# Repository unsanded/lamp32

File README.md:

<big>CC3000 wifi lamp</big>

Basically a lamp with 5 colours, a bulb, controlled over wifi.

Currently i am strugling with bugs in the cc3000 module. Even TI recomend using the cc3100 instead, but i already had my cc3000 module before that. 
I will try to update the firmware, because that might fix some bugs. I don't however have an official patch programmer.

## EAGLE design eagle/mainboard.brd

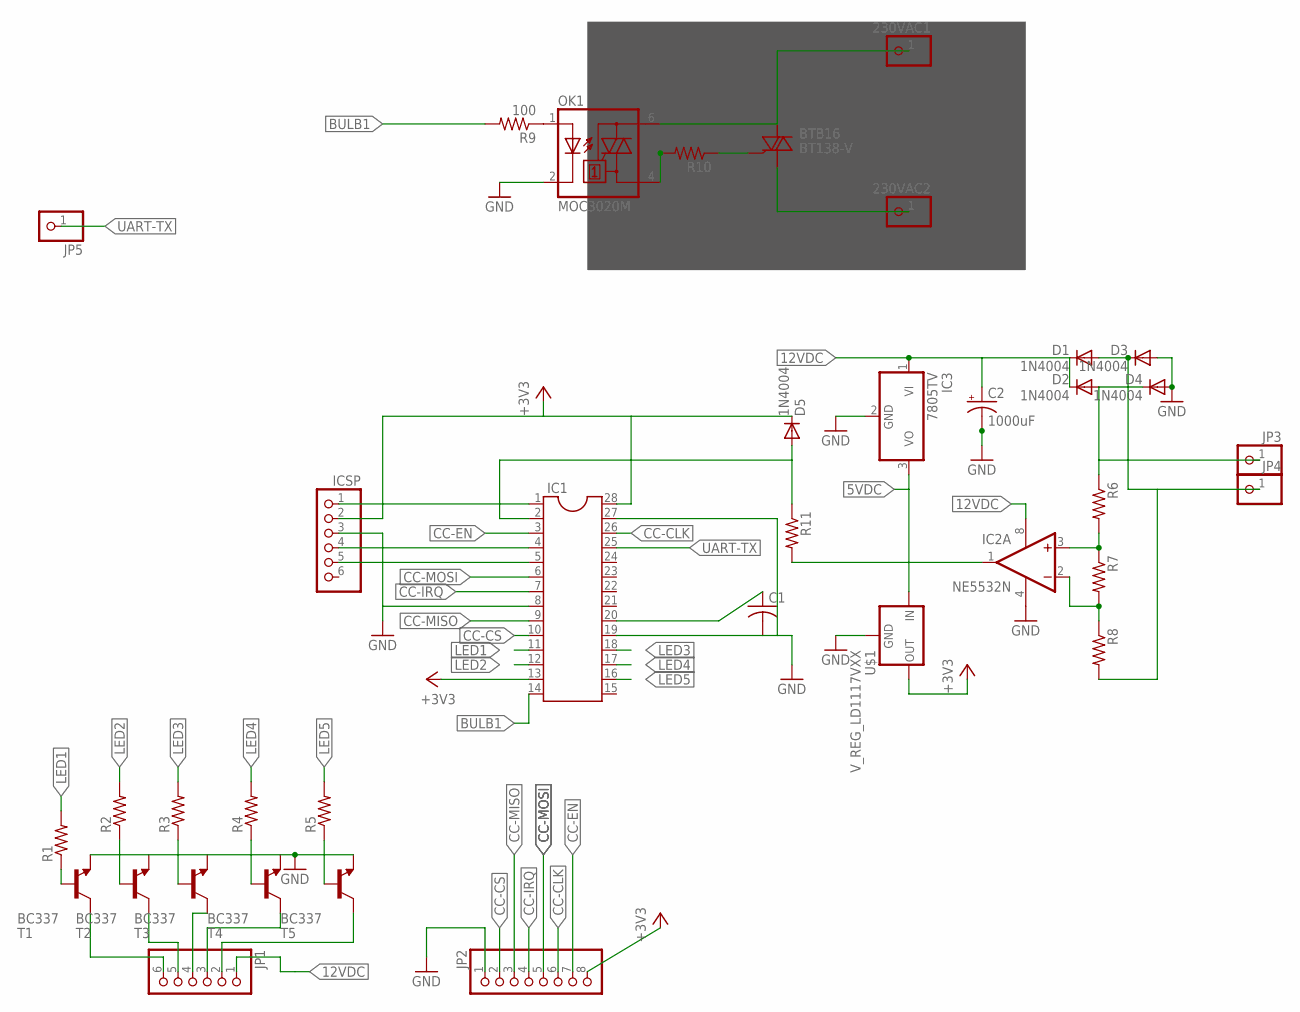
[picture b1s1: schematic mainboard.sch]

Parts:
230VAC1, 230VAC2: PINHD-1X1CB; 1X01-CLEANBIG
BTB16: BT138-V; TO220BV
C1: C-US025-024X044; C025-024X044
C2: 1000uF; B45181B; MPN 25ZL1000MEFC12.5X20
D1, D2, D3, D4, D5: 1N4004; DO41-10; MPN 1N4004
IC1: DIL28-3
IC2: NE5532N; DIL08; MPN NE5532AP
IC3: 7805TV; TO220V
ICSP: PINHD-1X6; 1X06
JP1: PINHD-1X6; 1X06
JP2: PINHD-1X8BIG; 1X08-BIG
JP3, JP4: PINHD-1X1CB; 1X01-CLEANBIG
JP5: PINHD-1X1; 1X01
OK1: MOC3020M; DIL06
R1, R2, R3, R4, R5, R10: R-US_0204/7; 0204/7
R6, R8, R11: R-US_0207/10; 0207/10
R7: R-US_0204/2V; 0204V
R9: 100; 0204/7
T1, T2, T3, T4, T5: BC337; TO92-EBC-OVAL; MPN BC33725TA
U$1: V_REG_LD1117VXX; 78XXL

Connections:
5VDC: IC3.3 (VO), U$1.OUT (IN)
12VDC: C2.+, D1.C, D2.C, IC2.8 (V+), IC3.1 (VI), JP1.1
+3V3: D5.C, IC1.13, IC1.28, ICSP.2, JP2.8, U$1.GND (OUT)
BULB1: IC1.14, R9.2
CC-CLK: IC1.26, JP2.6
CC-CS: IC1.10, JP2.2
CC-EN: IC1.3, JP2.7
CC-IRQ: IC1.7, JP2.4
CC-MISO: IC1.9, JP2.3
CC-MOSI: IC1.6, JP2.5
GND: C1.2, C2.-, D3.A, D4.A, IC1.8, IC1.19, IC1.27, IC2.4 (V-), IC3.2 (GND), ICSP.3, JP2.1, OK1.2 (C), T1.E, T5.E, U$1.IN (GND)
LED1: IC1.11, R1.2
LED2: IC1.12, R2.2
LED3: IC1.18, R3.2
LED4: IC1.17, R4.2
LED5: IC1.16, R5.2
unnamed: IC1.1, ICSP.1
unnamed: D2.A, D4.C, JP3.1, R6.1
unnamed: D1.A, D3.C, JP4.1, R8.2
unnamed: IC1.4, ICSP.4
unnamed: IC1.5, ICSP.5
unnamed: JP1.6, T1.C
unnamed: JP1.5, T2.C
unnamed: JP1.4, T3.C
unnamed: JP1.3, T4.C
unnamed: JP1.2, T5.C
unnamed: R1.1, T1.B
unnamed: R2.1, T2.B
unnamed: R3.1, T3.B
unnamed: R4.1, T4.B
unnamed: R5.1, T5.B
unnamed: C1.1, IC1.20
unnamed: IC2.3 (+IN), R6.2, R7.1
unnamed: IC2.2 (-IN), R7.2, R8.1
unnamed: D5.A, IC1.2, R11.1
unnamed: OK1.1 (A), R9.1
unnamed: OK1.4 (A1), R10.2
unnamed: 230VAC1.1, BTB16.T2 (A2), OK1.6 (A2)
unnamed: 230VAC2.1, BTB16.T1 (A1)
unnamed: BTB16.G, R10.1
unnamed: IC2.1 (OUT), R11.2
UART-TX: IC1.25, JP5.1

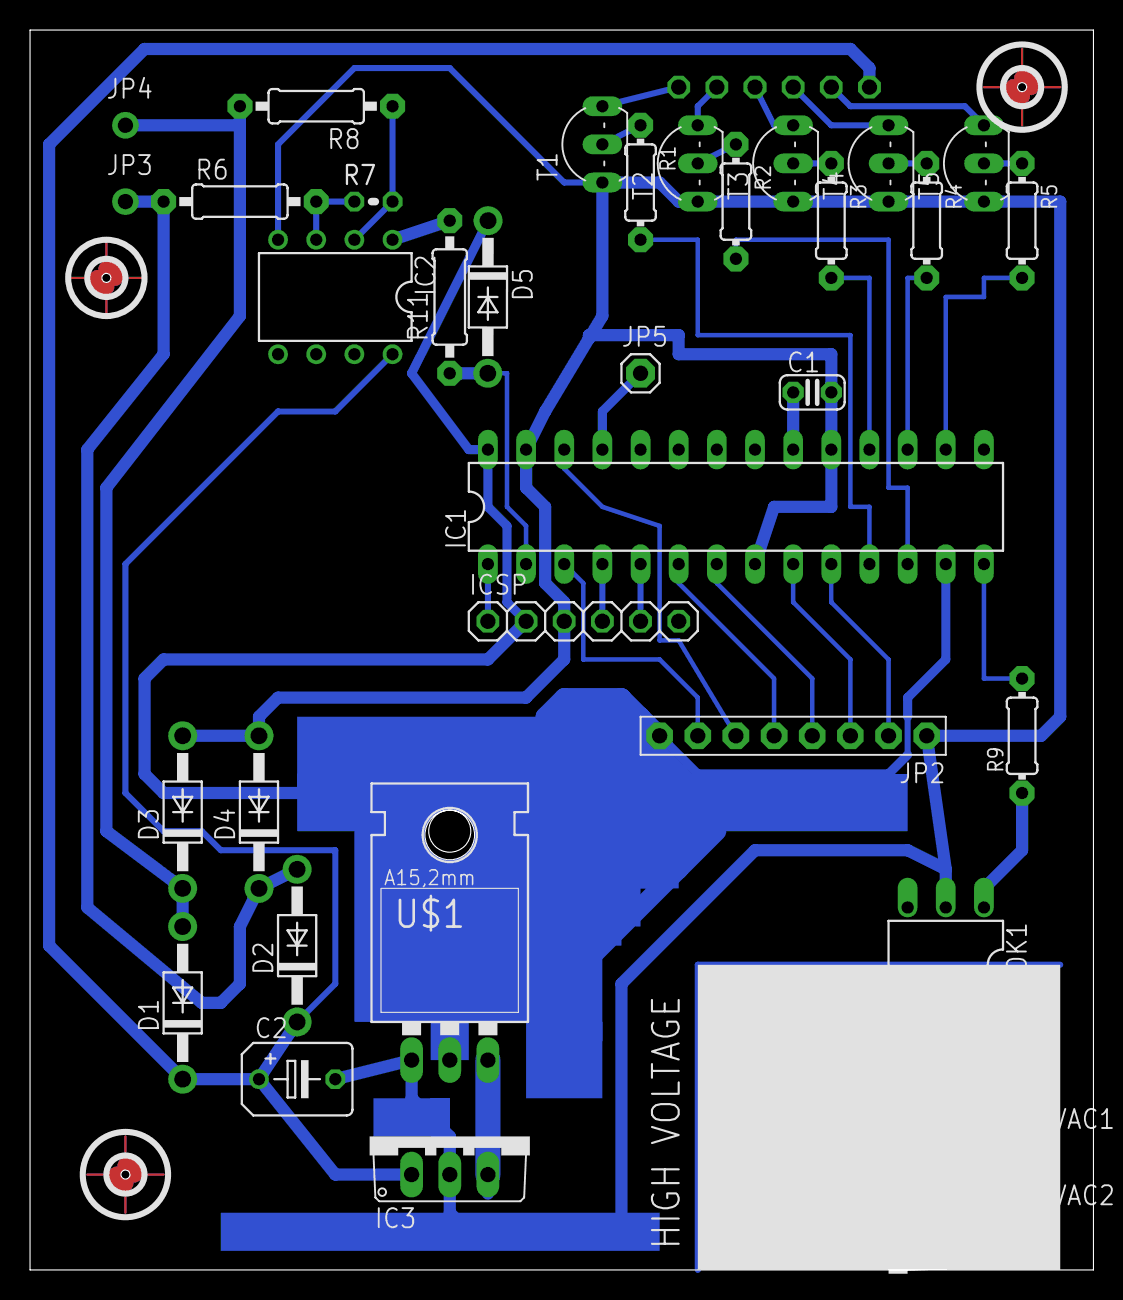
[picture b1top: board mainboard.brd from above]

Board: 2 copper layers, 70.8 x 82.5 mm, 40 parts (1 on the bottom side), 42 nets.

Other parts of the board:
U$3, U$4, U$5: PASS-ROUND

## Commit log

2014-09-25 Initial commit. Sockets work but are buggy.

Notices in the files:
parts and their libraries:
sparkfun-poweric: Licensing: Creative Commons ShareAlike 4.0 International - https://creativecommons.org/licenses/by-sa/4.0
